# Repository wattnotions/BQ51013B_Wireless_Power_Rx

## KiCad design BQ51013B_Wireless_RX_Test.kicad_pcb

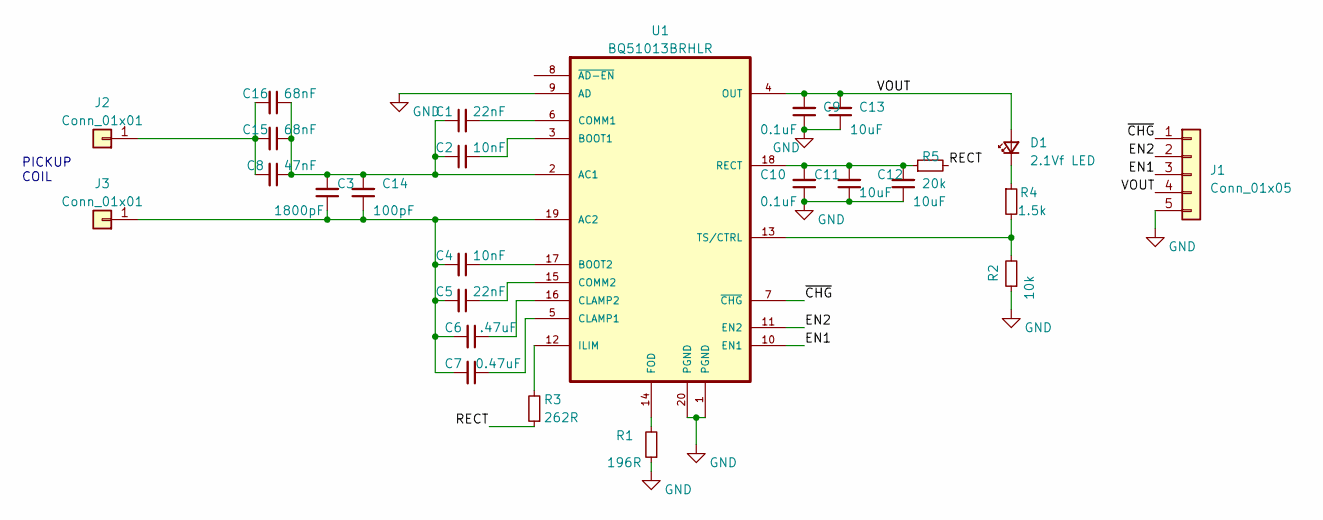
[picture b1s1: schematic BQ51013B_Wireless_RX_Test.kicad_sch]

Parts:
C1, C5: 22nF; C_0603_1608Metric
C2, C4: 10nF; C_0603_1608Metric
C3: 1800pF; C_0603_1608Metric
C6: .47uF; C_0603_1608Metric
C7: 0.47uF; C_0603_1608Metric
C8: 47nF; C_0603_1608Metric
C9, C10: 0.1uF; C_0603_1608Metric
C11, C12, C13: 10uF; C_0603_1608Metric
C14: 100pF; C_0603_1608Metric
C15, C16: 68nF; C_0603_1608Metric
D1: 2.1Vf LED; LED_0603_1608Metric
J1: Conn_01x05; MOLEX_0532610571
J2, J3: Conn_01x01; TestPoint_Pad_4.0x4.0mm
R1: 196R; R_0603_1608Metric
R2: 10k; R_0603_1608Metric
R3: 262R; R_0603_1608Metric
R4: 1.5k; R_0603_1608Metric
R5: 20k; R_0603_1608Metric
U1: BQ51013BRHLR; IC_MSP430FR2522IRHLR

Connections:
/EN1: J1.3, U1.10 (EN1)
/EN2: J1.2, U1.11 (EN2)
/RECT: R3.1, R5.2
/VOUT: C9.2, C13.2, D1.2 (A), J1.4, U1.4 (OUT)
/~CHG: J1.1, U1.7 (~CHG)
GND: C9.1, C10.1, C11.1, C12.1, C13.1, J1.5, R1.1, R2.1, U1.1 (PGND), U1.9 (AD), U1.20 (PGND), U1.22, U1.23, U1.24, U1.25, U1.26, U1.27, U1.28, U1.29
unnamed: D1.1 (K), R4.1
unnamed: C8.2, C15.2, C16.2, J2.1
unnamed: C3.1, C4.2, C5.2, C6.2, C7.2, C14.1, J3.1, U1.19 (AC2)
unnamed: C1.1, C2.1, C3.2, C8.1, C14.2, C15.1, C16.1, U1.2 (AC1)
unnamed: C2.2, U1.3 (BOOT1)
unnamed: C4.1, U1.17 (BOOT2)
unnamed: C7.1, U1.5 (CLAMP1)
unnamed: C6.1, U1.16 (CLAMP2)
unnamed: C1.2, U1.6 (COMM1)
unnamed: C5.1, U1.15 (COMM2)
unnamed: R1.2, U1.14 (FOD)
unnamed: R3.2, U1.12 (ILIM)
unnamed: C10.2, C11.2, C12.2, R5.1, U1.18 (RECT)
unnamed: R2.2, R4.2, U1.13 (TS/CTRL)

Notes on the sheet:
PICKUP COIL

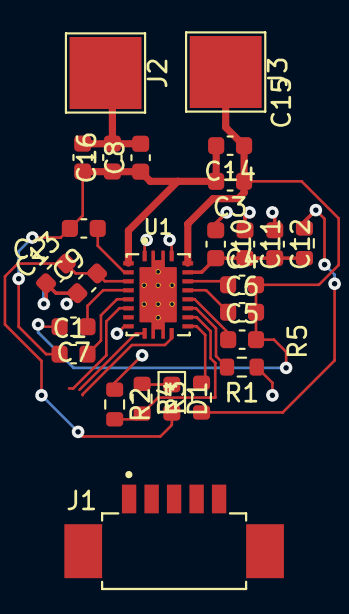
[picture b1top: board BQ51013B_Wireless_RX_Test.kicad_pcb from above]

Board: 2 copper layers, 26 parts (0 on the bottom side), 20 nets.

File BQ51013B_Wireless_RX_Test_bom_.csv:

Component,Description,Part,References,Value,Footprint,Quantity Per PCB,Datasheet,Availability,Check_prices,MF,MP,Package,Price,Purchase-URL,SnapEDA_Link
1,"Unpolarized capacitor, small symbol",C_Small,C14,100pF,,1,~,,,,,,,,
2,"Unpolarized capacitor, small symbol",C_Small,C3,1800pF,,1,~,,,,,,,,
3,"Unpolarized capacitor, small symbol",C_Small,C2 C4,10nF,,2,~,,,,,,,,
4,"Unpolarized capacitor, small symbol",C_Small,C1 C5,22nF,,2,~,,,,,,,,
5,"Unpolarized capacitor, small symbol",C_Small,C8 C15 C16,68nF,,3,~,,,,,,,,
6,"Unpolarized capacitor, small symbol",C_Small,C9 C10,0.1uF,,2,~,,,,,,,,
7,"Unpolarized capacitor, small symbol",C_Small,C6 C7,.47uF,,2,~,,,,,,,,
8,"Unpolarized capacitor, small symbol",C_Small,C11 C12 C13,10uF,,3,~,,,,,,,,
9,"Light emitting diode, small symbol",LED_Small,D1,2.1Vf LED,,1,~,,,,,,,,
10,"Generic connector, single row, 01x05, script generated (kicad-library-utils/schlib/autogen/connector/)",Conn_01x05,J1,Conn_01x05,,1,~,,,,,,,,
11,Inductor,L,PICKUP_COIL1,L,,1,~,,,,,,,,
12,"Resistor, small symbol",R_Small,R1,196R,,1,~,,,,,,,,
13,"Resistor, small symbol",R_Small,R3,262R,,1,~,,,,,,,,
14,"Resistor, small symbol",R_Small,R4,1.5k,,1,~,,,,,,,,
15,"Resistor, small symbol",R_Small,R2,10k,,1,~,,,,,,,,
16,"Resistor, small symbol",R_Small,R5,20k,,1,~,,,,,,,,
17,WPC 1.1 Compatible Fully integrated Wireless power Receiver IC,BQ51013BRHLR,U1,BQ51013BRHLR,IC_MSP430FR2522IRHLR,1,,In Stock,https://www.snapeda.com/parts/BQ51013BRHLR/Texas+Instruments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,Texas Instruments,BQ51013BRHLR,VQFN-20 Texas Instruments,None,https://www.snapeda.com/api/url_track_click_mouser/?unipart_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 Instruments&part_name=BQ51013BRHLR&search_term=None,https://www.snapeda.com/parts/BQ51013BRHLR/Texas+Instruments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





Component Groups:,17
Component Count:,25
Fitted Components:,25
Number of PCBs:,1
Total components:,25
Schematic Version:,
Schematic Date:,
PCB Variant:,default
BoM Date:,17/09/2023 17:47:55
Schematic Source:,BQ51013B_Wireless_RX_Test.kicad_sch
KiCad Version:,Eeschema (7.0.0)

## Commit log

2023-09-17 sch done, started on layout
2023-09-18 layout 85% done
